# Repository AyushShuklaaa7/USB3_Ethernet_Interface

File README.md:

# USB 3.1 Gen 1 to Gigabit Ethernet Interface

This project is a hardware implementation of a USB 3.1 Gen 1 to Gigabit Ethernet adapter designed in KiCad. It is based on the Microchip LAN7801 USB-to-Ethernet controller and the KSZ9031RNX Gigabit Ethernet PHY.

The goal of this project was to gain practical experience in designing a high-speed PCB while following signal integrity, power integrity, and layout guidelines required for USB 3.1 and Gigabit Ethernet interfaces.

---

# Overview

The LAN7801 acts as the USB 3.1 Gen 1 bridge and Ethernet MAC, converting 5 Gbps USB SuperSpeed data into a 125 MHz RGMII interface. The KSZ9031RNX then converts the RGMII data into standard Gigabit Ethernet signals that are transmitted through the RJ45 MagJack.

The design uses dedicated 3.3V and 1.2V power rails. Instead of using an external 1.2V regulator, the KSZ9031RNX's integrated LDO controller is used with a DMG2301L P-channel MOSFET to generate the PHY core supply, reducing the overall component count.

A 25 MHz ABM8G crystal provides the reference clock for both devices.

---

# PCB Layout

### Top Layer

---

### Bottom Layer

---

### 3D View

---

# Hardware Block Diagram

The USB Type-A connector interfaces with the LAN7801 controller. The controller communicates with the KSZ9031RNX Gigabit PHY over the RGMII interface, while MDIO/MDC is used for PHY configuration. The PHY then drives the RJ45 MagJack to provide a standard Gigabit Ethernet connection.

---

# Design Approach

The project started by studying the LAN7801 and KSZ9031RNX datasheets along with the manufacturer's reference designs to understand the required interfaces, power supplies, clocking, and layout recommendations.

After completing the schematic, component placement was planned carefully to keep high-speed signal paths as short as possible. The USB controller was placed close to the USB connector, while the Ethernet PHY was positioned near the RJ45 MagJack to minimize RGMII routing.

During PCB layout, the main focus was maintaining signal integrity by following controlled impedance routing, differential pair routing, length matching, proper grounding, and good decoupling practices.

---

# Main Components

| Component | Description |
|----------|-------------|
| LAN7801 | USB 3.1 Gen 1 to Gigabit Ethernet Controller |
| KSZ9031RNX | Gigabit Ethernet PHY |
| ABM8G | 25 MHz Crystal Oscillator |
| DMG2301L | P-Channel MOSFET |
| RJ45 MagJack | Gigabit Ethernet Connector |
| USB Type-A Connector | USB SuperSpeed Interface |

---

# PCB Design Highlights

- 4-layer PCB stack-up
- USB 3.1 SuperSpeed differential pair routing
- 125 MHz RGMII interface routing
- Controlled impedance traces
- Differential pair length matching
- Continuous ground plane
- Proper decoupling capacitor placement
- ESD protection for external interfaces
- Power integrity considerations

---

# Design Challenges

Some of the key challenges while designing this PCB were:

- Routing USB SuperSpeed differential pairs while maintaining impedance.
- Length matching the RGMII interface.
- Placing decoupling capacitors close to the IC power pins.
- Maintaining clean return current paths using continuous ground planes.
- Planning the component placement to minimize high-speed routing complexity.
- Following the layout recommendations provided in the component datasheets.

---

# Software Used

- KiCad
- Saturn PCB Toolkit
- Pspice

---

# Future Improvements

- Generate complete fabrication outputs (Gerber, Drill, BOM and Pick & Place files).
- Perform impedance verification using PCB stack-up calculations.
- Prototype and validate the hardware with functional testing.
- Perform USB and Ethernet compliance testing.

---

# Author

**Ayush Shukla**

B.Tech Electronics & Telecommunication Engineering

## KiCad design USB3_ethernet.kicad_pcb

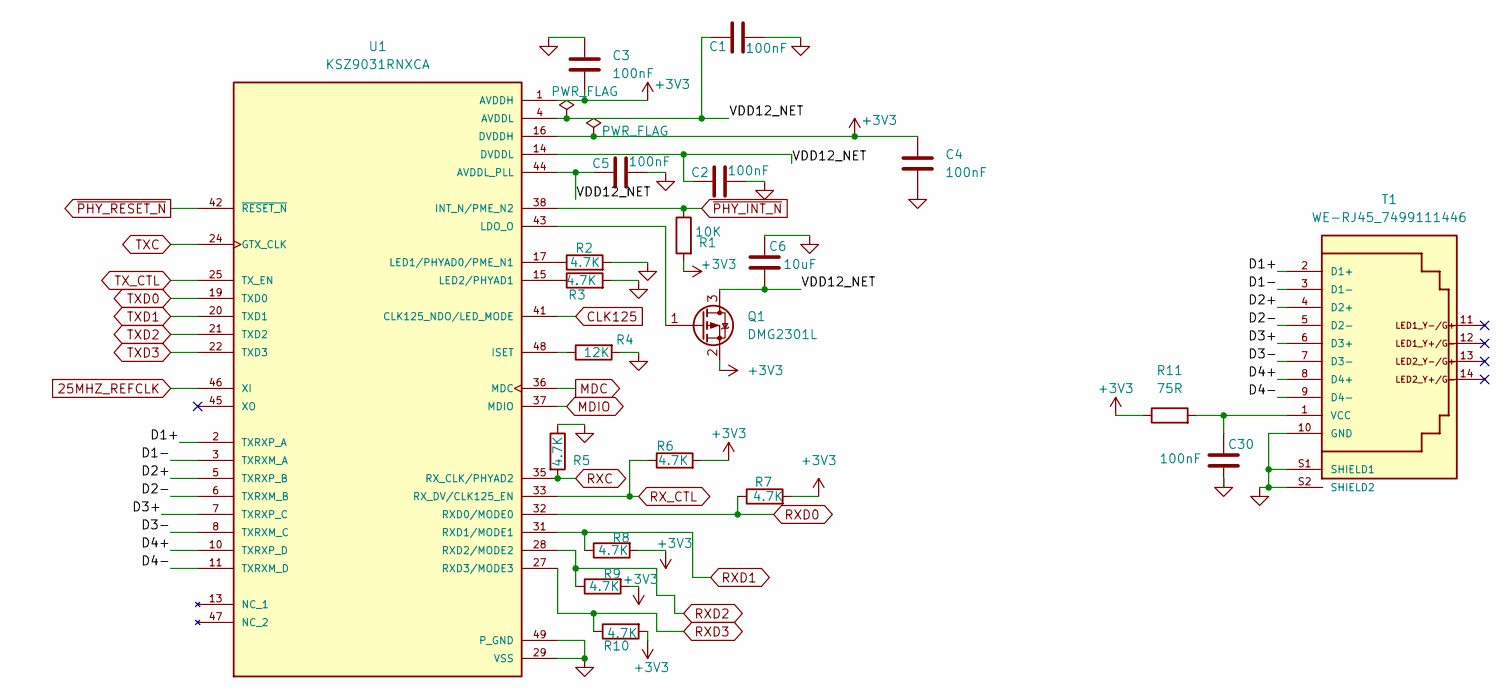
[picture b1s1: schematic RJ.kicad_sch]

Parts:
C1, C2, C3, C4, C5, C30: 100nF; C_0402_1005Metric
C6: 10uF; C_0805_2012Metric
Q1: DMG2301L; SOT-23
R1: 10K; R_0402_1005Metric
R2, R3, R5, R6, R7, R8, R9, R10: 4.7K; R_0402_1005Metric
R4: 12K; R_0402_1005Metric
R11: 75R; R_0402_1005Metric
T1: WE-RJ45_7499111446; RJ45_Wuerth_7499111446_Horizontal
U1: KSZ9031RNXCA; QFN-48-1EP_7x7mm_P0.5mm_EP5.15x5.15mm; PARTREV 07-09-24

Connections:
25MHZ_REFCLK: U1.46 (XI); also elsewhere on the board
/RJ/D1+: T1.2 (D1+), U1.2 (TXRXP_A); also elsewhere on the board
/RJ/D1-: T1.3 (D1-), U1.3 (TXRXM_A); also elsewhere on the board
/RJ/D2+: T1.4 (D2+), U1.5 (TXRXP_B); also elsewhere on the board
/RJ/D2-: T1.5 (D2-), U1.6 (TXRXM_B); also elsewhere on the board
/RJ/D3+: T1.6 (D3+), U1.7 (TXRXP_C); also elsewhere on the board
/RJ/D3-: T1.7 (D3-), U1.8 (TXRXM_C); also elsewhere on the board
/RJ/D4+: T1.8 (D4+), U1.10 (TXRXP_D); also elsewhere on the board
/RJ/D4-: T1.9 (D4-), U1.11 (TXRXM_D); also elsewhere on the board
AVDDL: C1.1, C2.1, C5.1, C6.2, Q1.3 (D), U1.4 (AVDDL), U1.9 (AVDDL), U1.14 (DVDDL), U1.18 (DVDDL), U1.23 (DVDDL), U1.26 (DVDDL), U1.30 (DVDDL), U1.39 (DVDDL), U1.44 (AVDDL_PLL)
CLK125: U1.41 (CLK125_NDO/LED_MODE); also elsewhere on the board
MDC: U1.36 (MDC); also elsewhere on the board
MDIO: U1.37 (MDIO); also elsewhere on the board
unnamed: Q1.1 (G), U1.43 (LDO_O)
unnamed 34: C30.1, R11.2, T1.1 (VCC); also elsewhere on the board
unnamed: R4.1, U1.48 (ISET)
unnamed: R2.1, U1.17 (LED1/PHYAD0/PME_N1)
unnamed: R3.1, U1.15 (LED2/PHYAD1)
RXC: R5.2, U1.35 (RX_CLK/PHYAD2); also elsewhere on the board
RXD0: R7.1, U1.32 (RXD0/MODE0); also elsewhere on the board
RXD1: R8.1, U1.31 (RXD1/MODE1); also elsewhere on the board
RXD2: R9.1, U1.28 (RXD2/MODE2); also elsewhere on the board
RXD3: R10.1, U1.27 (RXD3/MODE3); also elsewhere on the board
RX_CTL: R6.1, U1.33 (RX_DV/CLK125_EN); also elsewhere on the board
TXC: U1.24 (GTX_CLK); also elsewhere on the board
TXD0: U1.19 (TXD0); also elsewhere on the board
TXD1: U1.20 (TXD1); also elsewhere on the board
TXD2: U1.21 (TXD2); also elsewhere on the board
TXD3: U1.22 (TXD3); also elsewhere on the board
TX_CTL: U1.25 (TX_EN); also elsewhere on the board
VDD33A: C3.2, C4.1, Q1.2 (S), R1.2, R6.2, R7.2, R8.2, R9.2, R10.2, R11.1, U1.1 (AVDDH), U1.12 (AVDDH), U1.16 (DVDDH), U1.34 (DVDDH), U1.40 (DVDDH); also elsewhere on the board
~PHY_INT_N: R1.1, U1.38 (INT_N/PME_N2); also elsewhere on the board
~PHY_RESET_N: U1.42 (~RESET_N); also elsewhere on the board

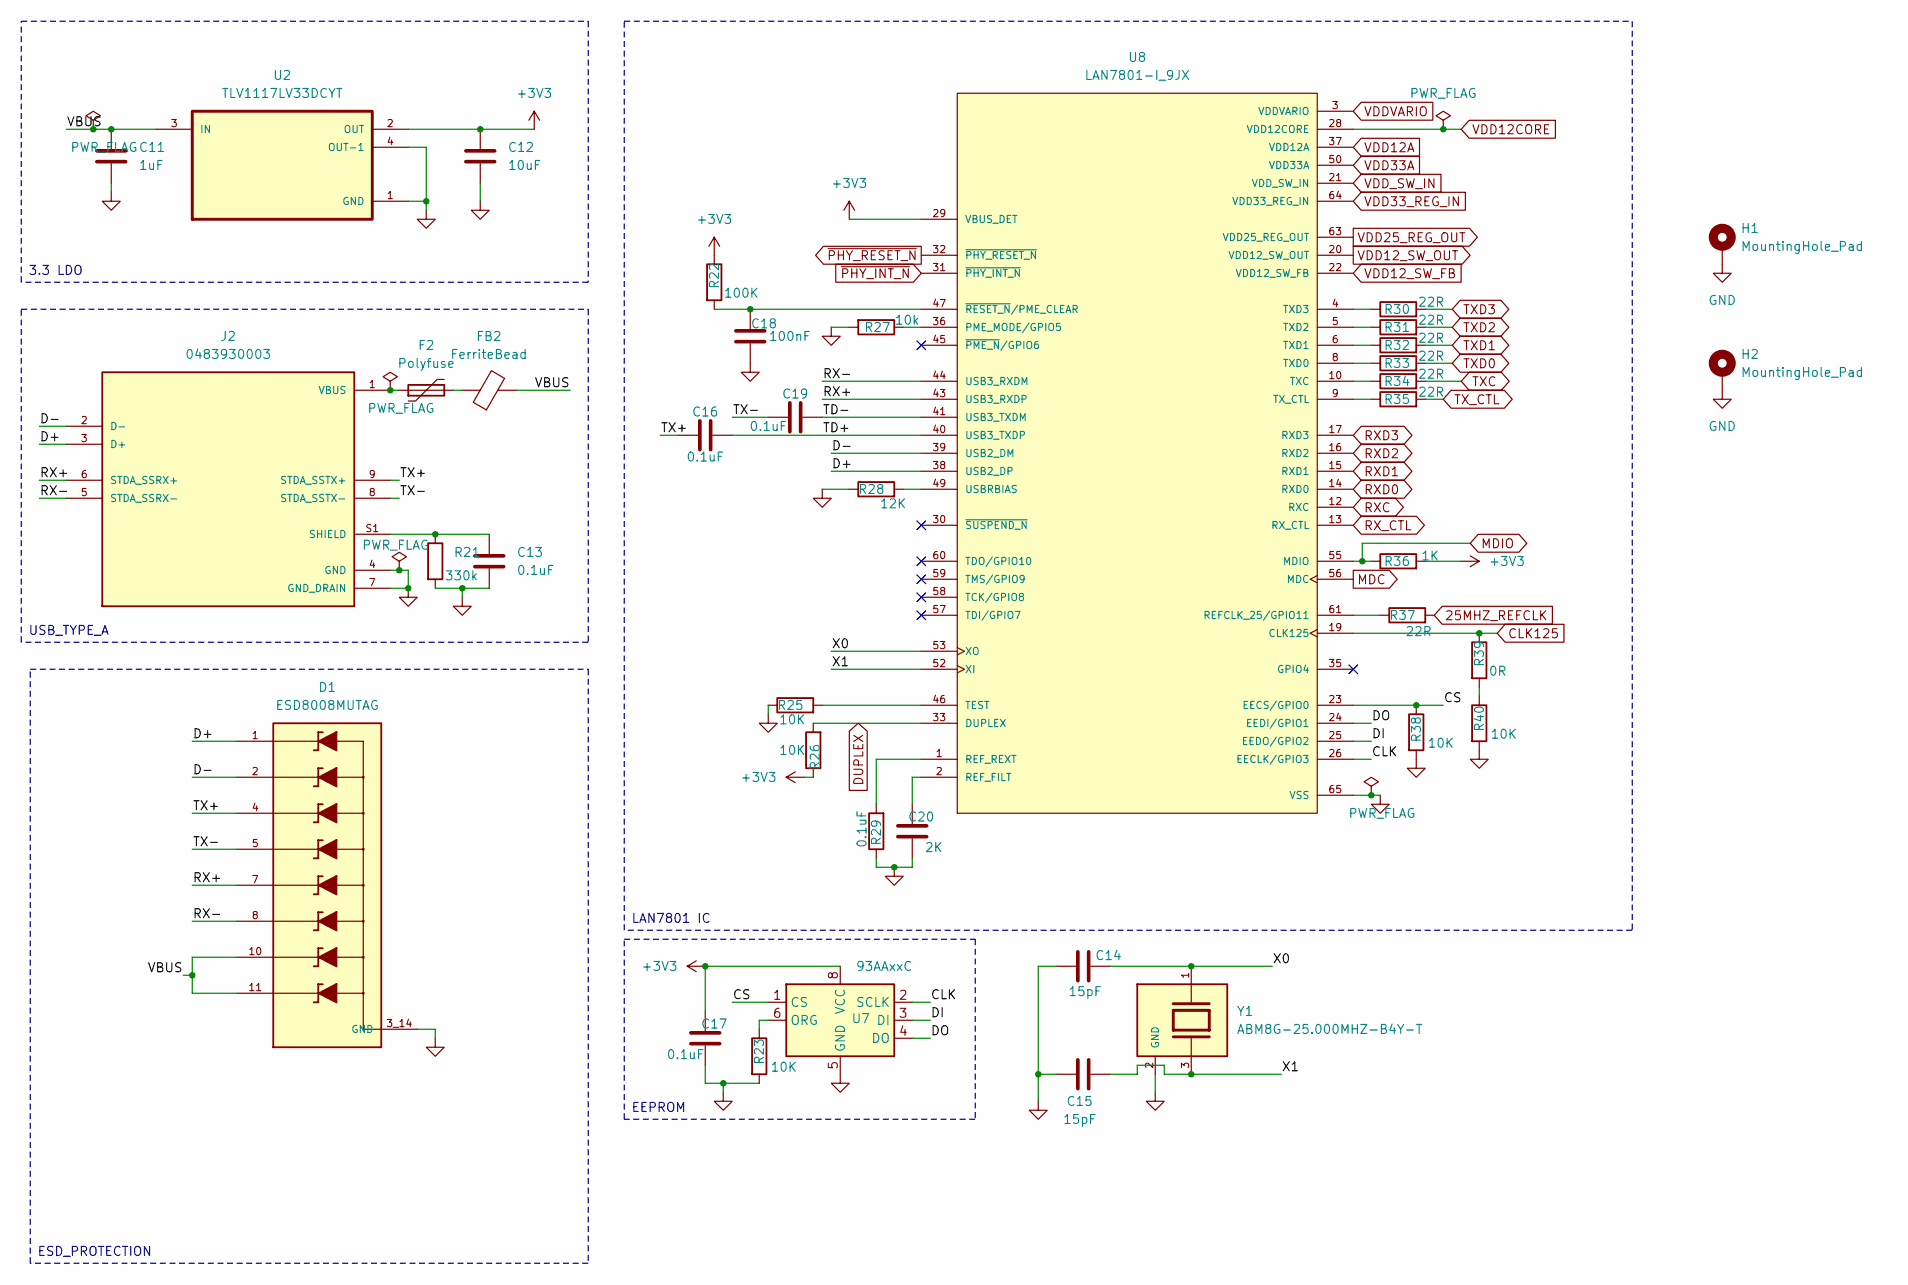
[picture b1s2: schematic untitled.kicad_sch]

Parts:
C11: 1uF; C_0402_1005Metric
C12: 10uF; C_0402_1005Metric
C13, C16, C17, C19: 0.1uF; C_0402_1005Metric
C14, C15: 15pF; C_0402_1005Metric
C18: 100nF; C_0402_1005Metric
C20: 2K; C_0402_1005Metric
D1: ESD8008MUTAG; DIO_ESD8008MUTAG; PARTREV 5
F2: Polyfuse; Fuse_0805_2012Metric
FB2: FerriteBead; L_0805_2012Metric
H1, H2: MountingHole_Pad; MountingHole_3.2mm_M3_Pad_Via
J2: 0483930003; USB3_A_Molex_48393-001; PARTREV A
R21: 330k; R_0402_1005Metric
R22: 100K; R_0402_1005Metric
R23, R25, R26, R38, R40: 10K; R_0402_1005Metric
R27: 10k; R_0402_1005Metric
R28: 12K; R_0402_1005Metric
R29: 0.1uF; R_0402_1005Metric
R30, R31, R32, R33, R34, R35, R37: 22R; R_0402_1005Metric
R36: 1K; R_0402_1005Metric
R39: 0R; R_0402_1005Metric
U2: TLV1117LV33DCYT; SOT230P700X180-4N
U7: 93AAxxC; SOIC-8_3.9x4.9mm_P1.27mm
U8: LAN7801-I_9JX; QFN50P900X900X100-65N_LAN7801-I_9JX; PARTREV DS00002123F; DigiKey_Part_Number LAN7801-I/9JX-ND
Y1: ABM8G-25.000MHZ-B4Y-T; Crystal_SMD_Abracon_ABM8G-4Pin_3.2x2.5mm; PARTREV 08.13.15

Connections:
25MHZ_REFCLK: R37.2; also elsewhere on the board
/USB/CLK: U7.2 (SCLK), U8.26 (EECLK/GPIO3)
/USB/CS: R38.1, U7.1 (CS), U8.23 (EECS/GPIO0)
/USB/D+: D1.1, J2.3 (D+), U8.38 (USB2_DP); also elsewhere on the board
/USB/D-: D1.2, J2.2 (D-), U8.39 (USB2_DM); also elsewhere on the board
/USB/DI: U7.3 (DI), U8.25 (EEDO/GPIO2)
/USB/DO: U7.4 (DO), U8.24 (EEDI/GPIO1)
/USB/RX+: D1.7, J2.6 (STDA_SSRX+), U8.43 (USB3_RXDP); also elsewhere on the board
/USB/RX-: D1.8, J2.5 (STDA_SSRX-), U8.44 (USB3_RXDM); also elsewhere on the board
/USB/TD+: C16.1, U8.40 (USB3_TXDP)
/USB/TD-: C19.2, U8.41 (USB3_TXDM)
/USB/TX+: C16.2, D1.4, J2.9 (STDA_SSTX+); also elsewhere on the board
/USB/TX-: C19.1, D1.5, J2.8 (STDA_SSTX-); also elsewhere on the board
/USB/VBUS: C11.1, D1.10, D1.11, FB2.2, U2.3 (IN)
/USB/X0: C14.1, U8.53 (XO), Y1.1
/USB/X1: C15.1, U8.52 (XI), Y1.3
CLK125: R39.1, U8.19 (CLK125); also elsewhere on the board
DUPLEX: R26.2, U8.33 (DUPLEX)
MDC: U8.56 (MDC); also elsewhere on the board
MDIO: R36.1, U8.55 (MDIO); also elsewhere on the board
unnamed: C13.1, J2.S1 (SHIELD), J2.S2 (SHIELD), J2.S3 (SHIELD), J2.S4 (SHIELD), R21.1
unnamed: F2.2, FB2.1
unnamed 31: F2.1, J2.1 (VBUS); also elsewhere on the board
unnamed: R39.2, R40.1
unnamed: R23.1, U7.6 (ORG)
unnamed: R27.1, U8.36 (PME_MODE/GPIO5)
unnamed: R37.1, U8.61 (REFCLK_25/GPIO11)
unnamed: C20.1, U8.2 (REF_FILT)
unnamed: R29.2, U8.1 (REF_REXT)
unnamed: R25.2, U8.46 (TEST)
unnamed: R34.1, U8.10 (TXC)
unnamed: R33.1, U8.8 (TXD0)
unnamed: R32.1, U8.6 (TXD1)
unnamed: R31.1, U8.5 (TXD2)
unnamed: R30.1, U8.4 (TXD3)
unnamed: R35.1, U8.9 (TX_CTL)
unnamed: R28.2, U8.49 (USBRBIAS)
unnamed: C18.2, R22.2, U8.47 (~RESET_N/PME_CLEAR)
RXC: U8.12 (RXC); also elsewhere on the board
RXD0: U8.14 (RXD0); also elsewhere on the board
RXD1: U8.15 (RXD1); also elsewhere on the board
RXD2: U8.16 (RXD2); also elsewhere on the board
RXD3: U8.17 (RXD3); also elsewhere on the board
RX_CTL: U8.13 (RX_CTL); also elsewhere on the board
TXC: R34.2; also elsewhere on the board
TXD0: R33.2; also elsewhere on the board
TXD1: R32.2; also elsewhere on the board
TXD2: R31.2; also elsewhere on the board
TXD3: R30.2; also elsewhere on the board
TX_CTL: R35.2; also elsewhere on the board
VDD12A: U8.28 (VDD12CORE), U8.37 (VDD12A), U8.42 (VDD12A), U8.54 (VDD12CORE), U8.62 (VDD12A); also elsewhere on the board
VDD12_SW_FB: U8.22 (VDD12_SW_FB); also elsewhere on the board
VDD12_SW_OUT: U8.20 (VDD12_SW_OUT); also elsewhere on the board
VDD25_REG_OUT: U8.63 (VDD25_REG_OUT); also elsewhere on the board
VDD33A: C12.1, C17.1, R22.1, R26.1, R36.2, U2.2 (OUT), U7.8 (VCC), U8.3 (VDDVARIO), U8.7 (VDDVARIO), U8.11 (VDDVARIO), U8.18 (VDDVARIO), U8.21 (VDD_SW_IN), U8.27 (VDDVARIO), U8.29 (VBUS_DET), U8.48 (VDDVARIO), U8.50 (VDD33A), U8.51 (VDDVARIO), U8.64 (VDD33_REG_IN); also elsewhere on the board
~PHY_INT_N: U8.31 (~PHY_INT_N); also elsewhere on the board
~PHY_RESET_N: U8.32 (~PHY_RESET_N); also elsewhere on the board

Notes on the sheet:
LAN7801 IC
3.3 LDO
ESD_PROTECTION
USB_TYPE_A
EEPROM

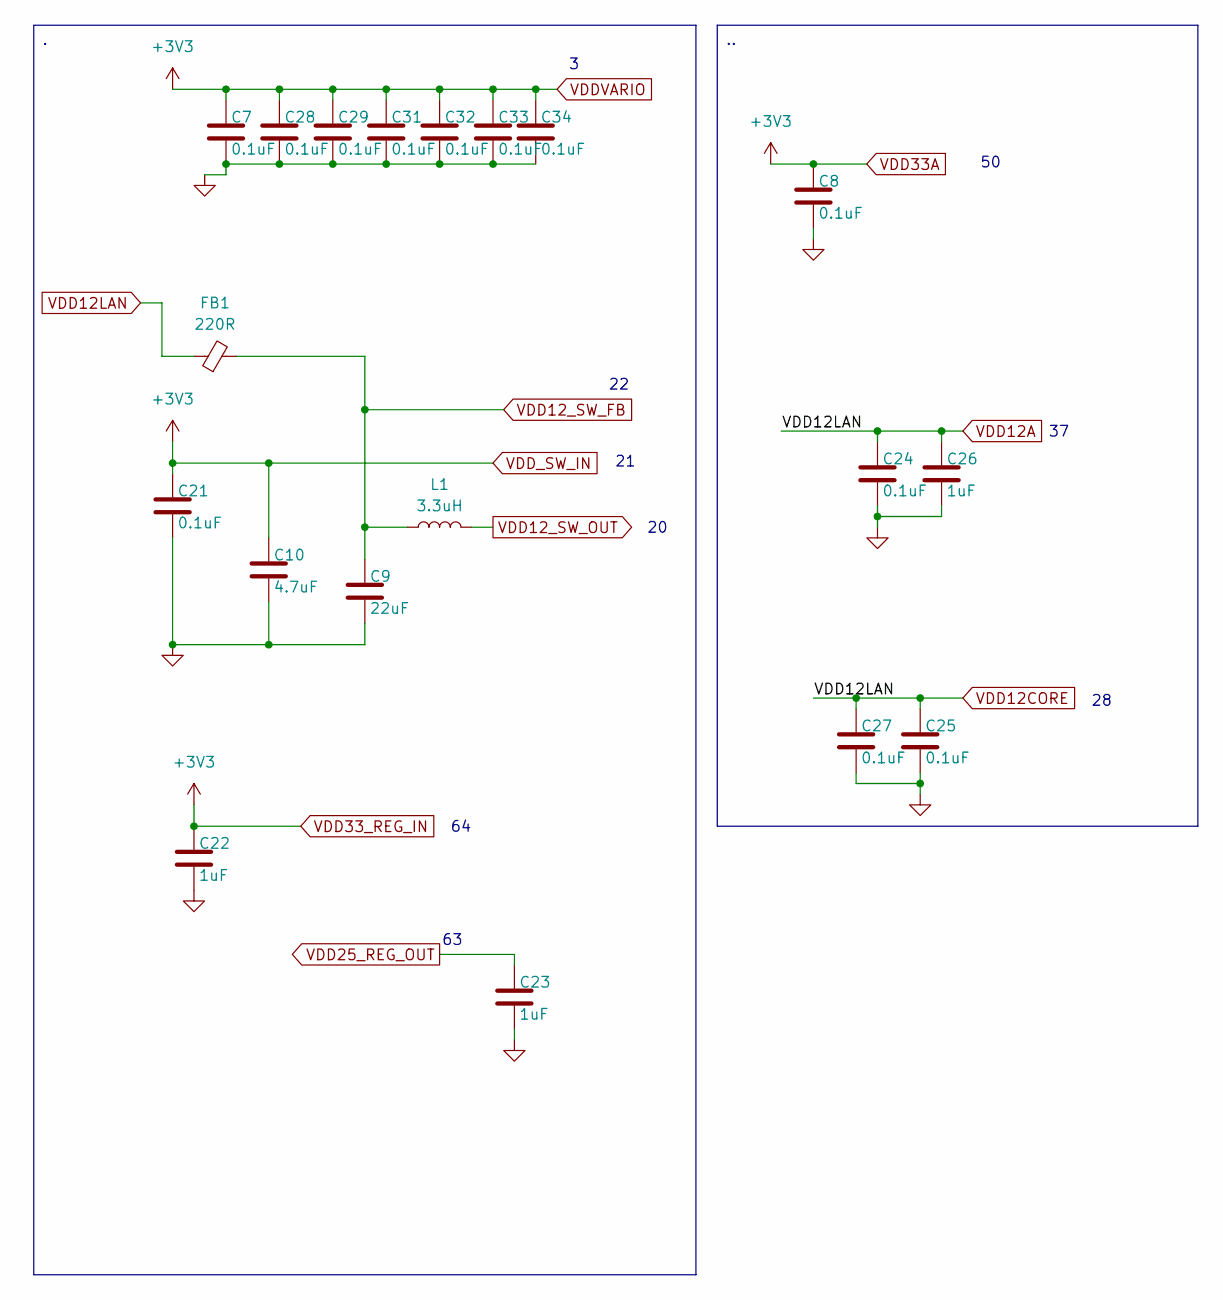
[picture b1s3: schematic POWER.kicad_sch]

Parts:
C7, C8, C21, C24, C25, C27, C28, C29, C31, C32, C33, C34: 0.1uF; C_0402_1005Metric
C9: 22uF; C_0402_1005Metric
C10: 4.7uF; C_0402_1005Metric
C22, C23, C26: 1uF; C_0402_1005Metric
FB1: 220R; L_0805_2012Metric
L1: 3.3uH; IND_ME3220-102MLB

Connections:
VDD12A: C24.1, C25.1, C26.1, C27.1, FB1.1; also elsewhere on the board
VDD12_SW_FB: C9.1, FB1.2, L1.1; also elsewhere on the board
VDD12_SW_OUT: L1.2; also elsewhere on the board
VDD25_REG_OUT: C23.1; also elsewhere on the board
VDD33A: C7.1, C8.1, C10.1, C21.1, C22.1, C28.1, C29.1, C31.1, C32.1, C33.1, C34.1; also elsewhere on the board

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
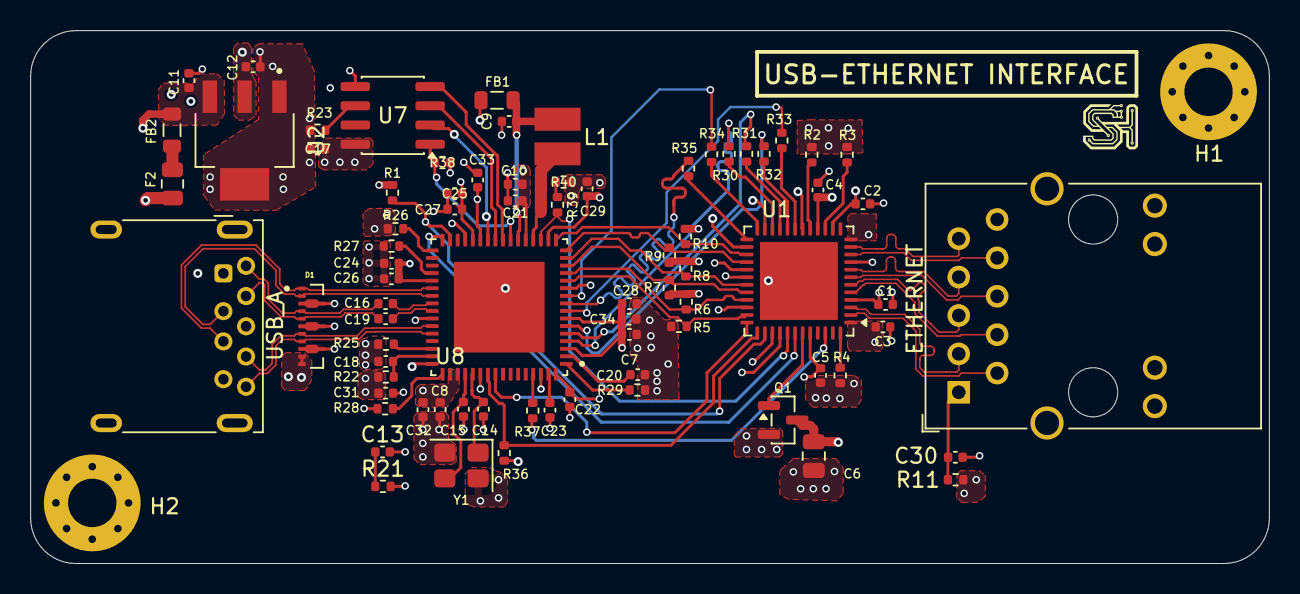
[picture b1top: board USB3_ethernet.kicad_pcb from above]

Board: 4 copper layers, 81.9 x 35.3 mm, 79 parts (0 on the bottom side), 72 nets.

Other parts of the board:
ETHERNET : WE-RJ45_7499111446; RJ45_Wuerth_7499111446_Horizontal
USB_A: 0483930003; USB3_A_Molex_48393-001

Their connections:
/RJ/D1+: ETHERNET.2 (D1+); also elsewhere on the board
/RJ/D1-: ETHERNET.3 (D1-); also elsewhere on the board
/RJ/D2+: ETHERNET.4 (D2+); also elsewhere on the board
/RJ/D2-: ETHERNET.5 (D2-); also elsewhere on the board
/RJ/D3+: ETHERNET.6 (D3+); also elsewhere on the board
/RJ/D3-: ETHERNET.7 (D3-); also elsewhere on the board
/RJ/D4+: ETHERNET.8 (D4+); also elsewhere on the board
/RJ/D4-: ETHERNET.9 (D4-); also elsewhere on the board
/USB/D+: USB_A.3 (D+); also elsewhere on the board
/USB/D-: USB_A.2 (D-); also elsewhere on the board
/USB/RX+: USB_A.6 (STDA_SSRX+); also elsewhere on the board
/USB/RX-: USB_A.5 (STDA_SSRX-); also elsewhere on the board
/USB/TX+: USB_A.9 (STDA_SSTX+); also elsewhere on the board
/USB/TX-: USB_A.8 (STDA_SSTX-); also elsewhere on the board
unnamed 31: USB_A.1 (VBUS); also elsewhere on the board
unnamed 34: ETHERNET.1 (VCC); also elsewhere on the board
